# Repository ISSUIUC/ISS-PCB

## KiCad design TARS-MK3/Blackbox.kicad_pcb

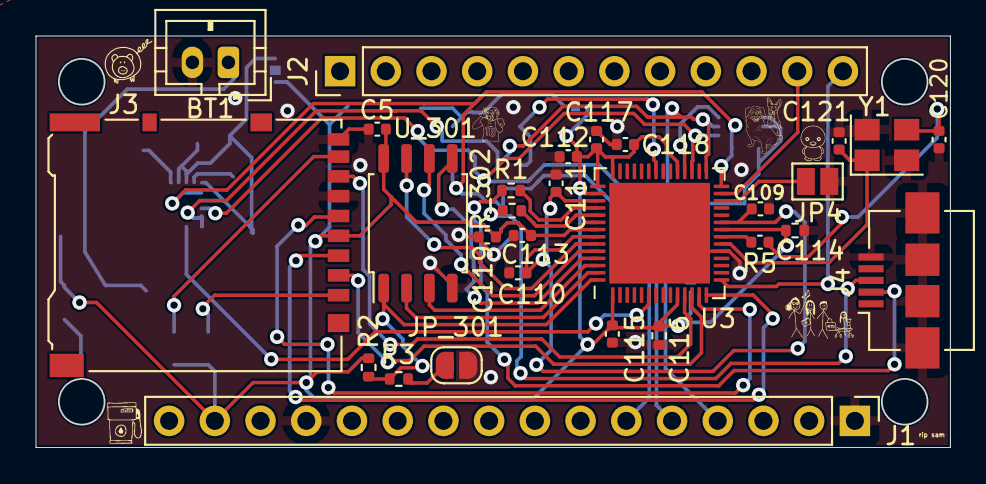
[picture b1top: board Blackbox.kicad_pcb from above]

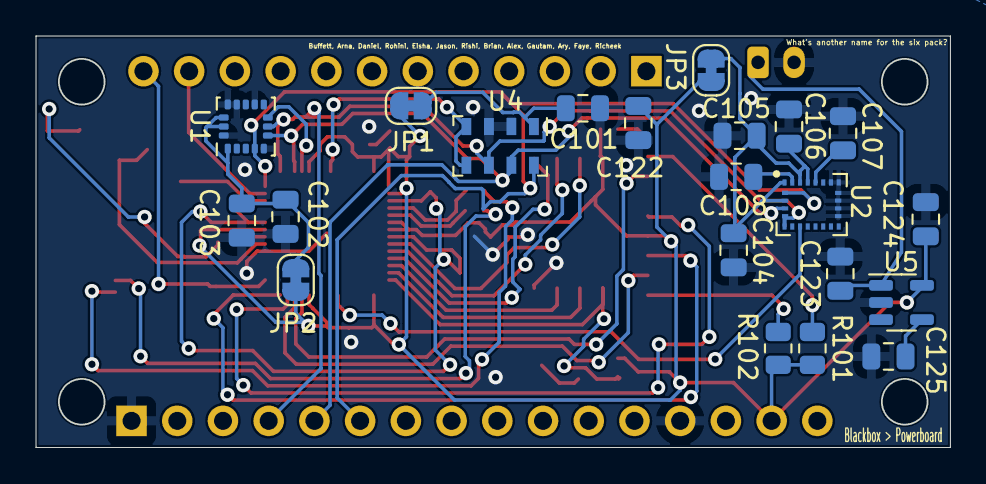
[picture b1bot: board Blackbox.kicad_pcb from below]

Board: 2 copper layers, 50.8 x 22.9 mm, 50 parts (21 on the bottom side), 39 nets.

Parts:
BT1: LiPo; JST_PH_B2B-PH-K_1x02_P2.00mm_Vertical
C5, C109, C110, C113, C115, C117, C118, C119: 100n; C_0402_1005Metric
C101: 100nF; C_0805_2012Metric
C102: 10uF; C_0805_2012Metric
C103: 0.1uF; C_0805_2012Metric
C104, C105, C108, C122: 100 nF; C_0805_2012Metric
C106: 10 uF; C_0805_2012Metric
C107: 10 nF; C_0805_2012Metric
C111, C112: 1u; C_0402_1005Metric
C114, C116: 100n; R_0402_1005Metric
C120, C121: LOAD_C; C_0402_1005Metric
C123, C124: 1uF; C_0805_2012Metric
C125: 10nF; C_0805_2012Metric
J1: RP Header 16 pin; PinHeader_1x16_P2.54mm_Vertical
J2: RP Header 12 pin; PinHeader_1x12_P2.54mm_Vertical
J3: Micro_SD_Card; microSD_HC_Hirose_DM3AT-SF-PEJM5
J4: USB_B_Micro; USB_Micro-B_Amphenol_10104110_Horizontal
JP1, JP2, JP3: Jumper_NC_Small; SolderJumper-2_P1.3mm_Bridged_RoundedPad1.0x1.5mm
JP4: Jumper; SolderJumper-2_P1.3mm_Open_Pad1.0x1.5mm
JP_301: Jumper; SolderJumper-2_P1.3mm_Open_RoundedPad1.0x1.5mm
R1: 27.4; R_0402_1005Metric
R2: DNF; R_0402_1005Metric
R3: R; R_0402_1005Metric
R5: 1k; C_0402_1005Metric
R101, R102: 10k; R_0805_2012Metric
R_302: 27.4; R_0402_1005Metric
U1: H3LIS331DL; LGA-16_3x3mm_P0.5mm_LayoutBorder3x5y
U2: LSM9DS1; LGA-24L_3x3.5mm_P0.43mm
U3: RP2040_chip; QFN-56-1EP_7x7mm_P0.4mm_EP5.6x5.6mm
U4: MS5611-01BA; LGA-8_3x5mm_P1.25mm
U5: LD3985M33R_SOT23; SOT-23-5
U_301: W25Q128JVS; SOIC-8_5.23x5.23mm_P1.27mm
Y1: Crystal_GND24; Crystal_SMD_3225-4Pin_3.2x2.5mm

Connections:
+1V1: C109.1, C110.1, C111.1, U3.23 (DVDD), U3.45 (VREG_VOUT), U3.50 (DVDD)
+3V3: C5.1, C112.1, C113.1, C114.1, C115.1, C116.1, C117.1, C118.1, C119.1, C122.2, C124.1, J1.15, J3.4 (VDD), JP1.1, JP2.1, JP3.1, R2.1, R101.1, R102.1, U3.1 (IOVDD), U3.10 (IOVDD), U3.22 (IOVDD), U3.33 (IOVDD), U3.42 (IOVDD), U3.43 (ADC_AVDD), U3.44 (VREG_VIN), U3.48 (USB_VDD), U3.49 (IOVDD), U5.5 (VOUT), U_301.8 (VCC)
/H3LIS331DL_CS: U1.8 (CS), U3.32 (GPIO21)
/I2C0_SCL: J2.11, U3.27 (GPIO16)
/I2C1_SDA: J2.12, U3.15 (GPIO12)
/LSM9_CS_M: U2.8 (CS_M), U3.6 (GPIO4)
/MS5611_CS: U3.36 (GPIO24), U4.4 (CSB), U4.5 (CSB)
/SNS_SPI_MISO: J1.4, U1.7 (SA0/SDO), U2.5 (SDO_A/G), U2.6 (SDO_M), U3.29 (GPIO18), U4.6 (SDO)
/SNS_SPI_MOSI: J1.5, U1.6 (SDA/SDI), U2.4 (SDA/SDI/SDO), U3.31 (GPIO20), U4.7 (SDI/SDA)
/SNS_SPI_SCK: J1.6, U1.4 (SCL/SCK), U2.2 (SCL/SPC), U3.28 (GPIO17), U4.8 (SCLK)
/SPI_SDCARD_CS: J3.2 (DAT3/CD), U3.12 (GPIO9)
/SPI_SDCARD_MISO: J3.7 (DAT0), U3.11 (GPIO8)
/SPI_SDCARD_MOSI: J3.3 (CMD), U3.14 (GPIO11)
/SPI_SDCARD_SCK: J3.5 (CLK), U3.13 (GPIO10)
/USB_D+: J4.3 (D+), R_302.1
/USB_D-: J4.2 (D-), R1.1
GND: BT1.2 (-), C5.2, C101.1, C102.2, C103.2, C104.2, C105.2, C106.2, C107.2, C108.2, C109.2, C110.2, C111.2, C112.2, C113.2, C114.2, C115.2, C116.2, C117.2, C118.2, C119.2, C120.2, C121.2, C122.1, C123.2, C124.2, C125.1, J1.1, J1.13, J3.6 (VSS), J3.9 (SHIELD), J4.5 (GND), J4.6 (Shield), JP4.1, JP_301.1, U1.5 (GND), U1.10 (GND), U1.12 (GND), U1.13 (GND), U1.16 (GND), U2.14 (RES), U2.15 (RES), U2.16 (RES), U2.17 (RES), U2.18 (RES), U2.19 (GND), U3.19 (TESTEN), U3.57 (GND), U4.2 (PS), U4.3 (GND), U5.2 (GND), U_301.4 (GND), Y1.2, Y1.4
unnamed: C101.2, JP1.2, U4.1 (VDD)
unnamed: C102.1, C103.1, JP2.2, U1.1 (VDDIO), U1.14 (VDD), U1.15 (VDD)
unnamed: C104.1, C105.1, C106.1, JP3.2, U2.1 (VDDIO), U2.3 (VDDIO), U2.22 (VDD), U2.23 (VDD)
unnamed: C107.1, U2.21 (CAP)
unnamed: C108.1, U2.24 (C1)
unnamed: C120.1, R5.2, Y1.3
unnamed: C121.1, U3.20 (XIN), Y1.1
unnamed: C125.2, U5.4 (BYP)
unnamed: J3.1 (DAT2), R102.2
unnamed: J3.8 (DAT1), R101.2
unnamed: JP4.2, U3.26 (RUN)
unnamed: JP_301.2, R3.1
unnamed: R1.2, U3.46 (USB_DM)
unnamed: R2.2, R3.2, U3.56 (QSPI_SS_N), U_301.1 (~CS)
unnamed: R5.1, U3.21 (XOUT)
unnamed: R_302.2, U3.47 (USB_DP)
unnamed: U3.51 (QSPI_SD3), U_301.7 (IO3)
unnamed: U3.52 (QSPI_SCLK), U_301.6 (CLK)
unnamed: U3.53 (QSPI_SD0), U_301.5 (DI(IO0))
unnamed: U3.54 (QSPI_SD2), U_301.3 (IO2)
unnamed: U3.55 (QSPI_SD1), U_301.2 (DO(IO1))
VBAT: BT1.1 (+), C123.1, U5.1 (VIN)

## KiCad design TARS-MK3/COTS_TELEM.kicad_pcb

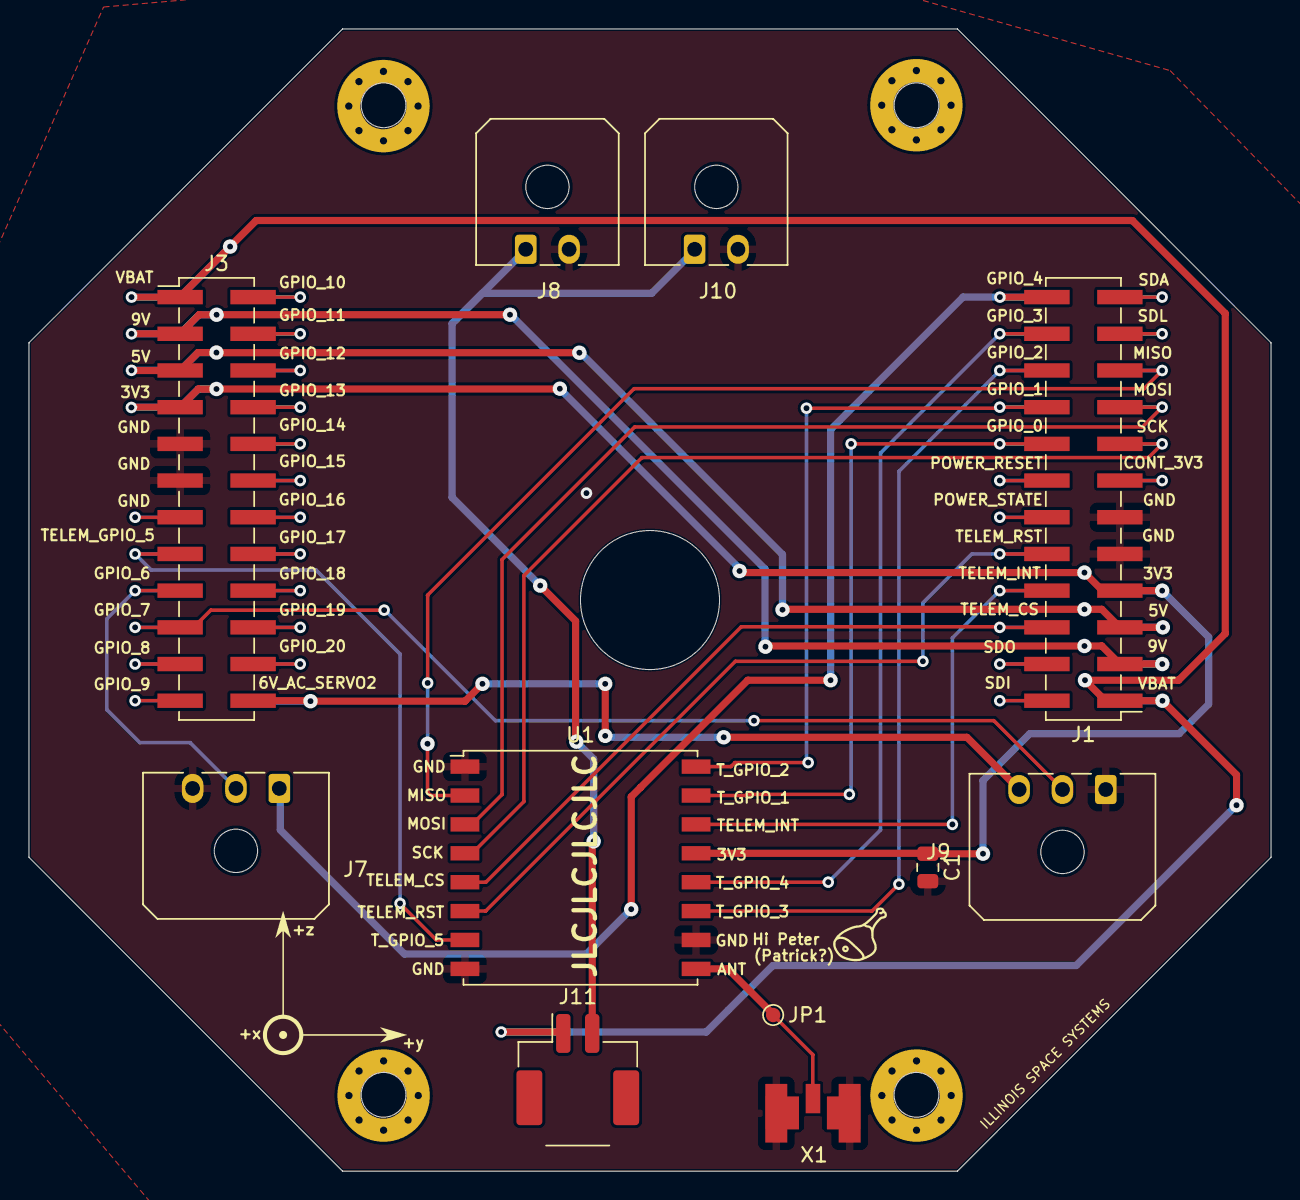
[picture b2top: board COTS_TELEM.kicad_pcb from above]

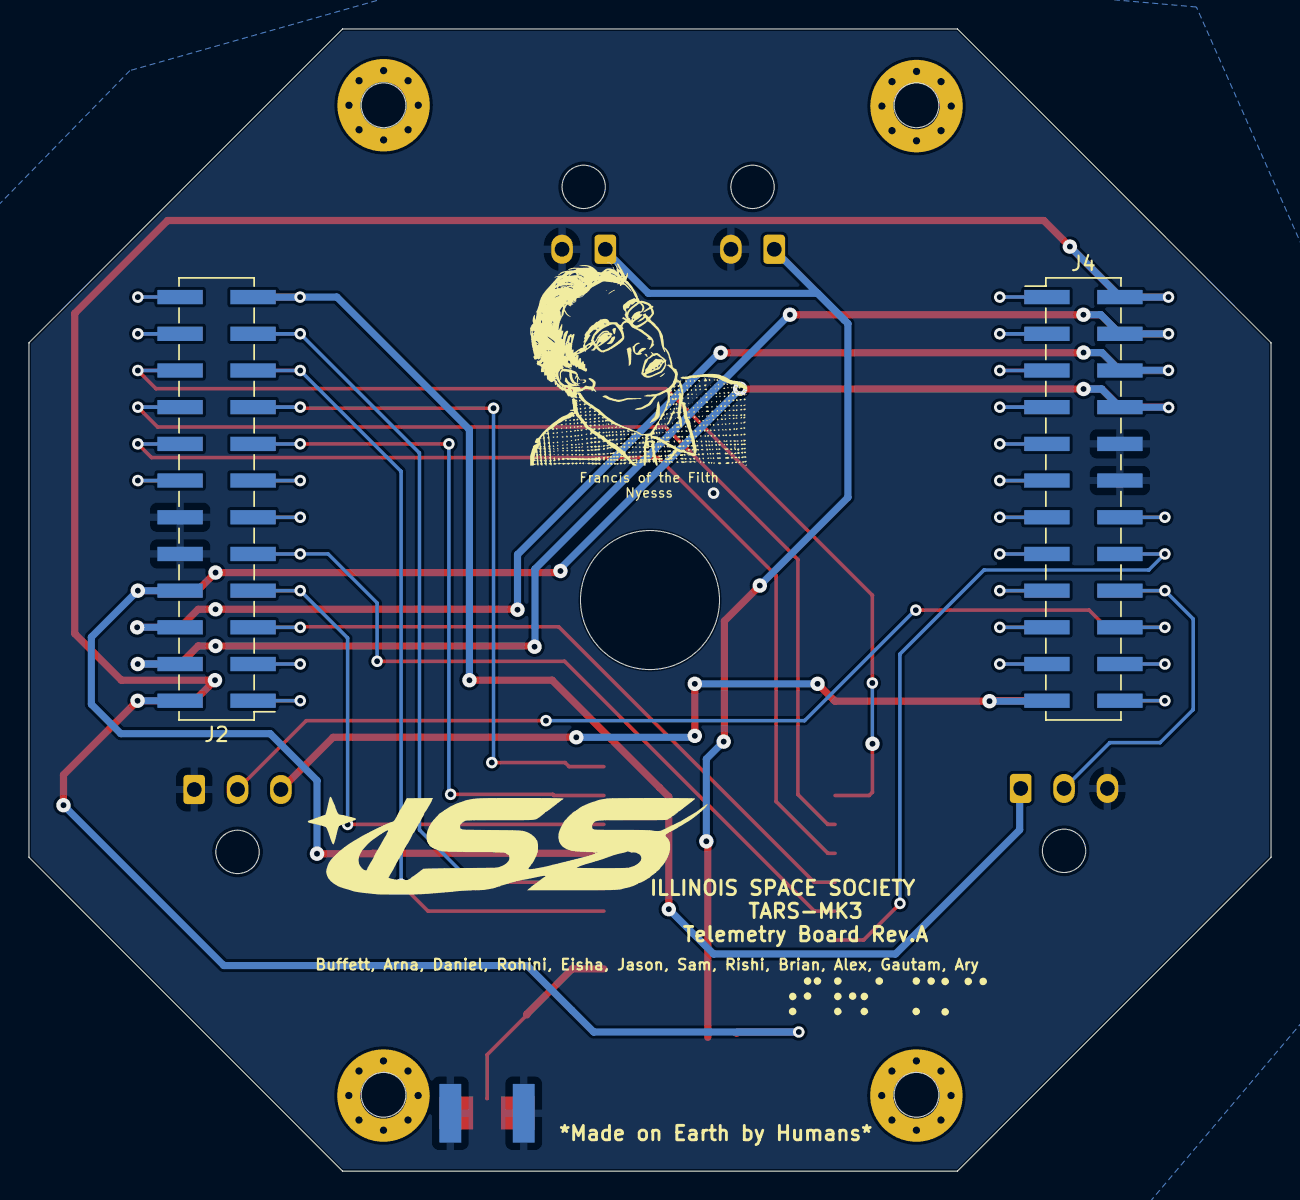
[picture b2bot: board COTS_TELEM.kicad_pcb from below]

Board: 2 copper layers, 86.0 x 79.1 mm, 13 parts (2 on the bottom side), 43 nets.

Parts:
C1: 10uF; C_0805_2012Metric
J1, J2, J3, J4: Conn_02x12_Odd_Even; PinHeader_2x12_P2.54mm_Vertical_SMD
J7, J9: Conn_01x03; Molex_Micro-Fit_3.0_43650-0300_1x03_P3.00mm_Horizontal
J8, J10: Conn_01x02; Molex_Micro-Fit_3.0_43650-0200_1x02_P3.00mm_Horizontal
J11: Conn_01x02; Molex_CLIK-Mate_502494-0270_1x02-1MP_P2.00mm_Horizontal
JP1: Conn_01x01_Female; TestPoint_Pad_D1.0mm
U1: RFM96W-433S2; HOPERF_RFM9XW_SMD
X1: uFL/SMA; uFL

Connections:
6V_AC_SERVO1: J1.24, J2.23, J7.1
6V_AC_SERVO2: J3.24, J4.23, J9.3
/3V3: C1.1, J1.7, J2.8, J3.7, J4.8, U1.13 (3.3V)
/5V: J1.5, J2.6, J3.5, J4.6
/9V: J1.3, J2.4, J3.3, J4.4
/B2B_GPIO_8: J3.21, J4.22
/B2B_GPIO_9: J3.23, J4.24
/B2B_GPIO_10: J3.2, J4.1
/B2B_GPIO_11: J3.4, J4.3
/B2B_GPIO_12: J3.6, J4.5
/B2B_GPIO_13: J3.8, J4.7
/B2B_GPIO_14: J3.10, J4.9
/B2B_GPIO_15: J3.12, J4.11
/B2B_GPIO_16: J3.14, J4.13
/B2B_GPIO_17: J3.16, J4.15
/B2B_GPIO_18: J3.18, J4.17
/B2B_GPIO_19: J3.20, J4.19
/B2B_GPIO_20: J3.22, J4.21
/B2B_I2C_SCL: J1.21, J2.22
/B2B_I2C_SDA: J1.23, J2.24
/B2B_SPI_MISO: J1.19, J2.20, U1.2 (MISO)
/B2B_SPI_MOSI: J1.17, J2.18, U1.3 (MOSI)
/B2B_SPI_SCK: J1.15, J2.16, U1.4 (SCK)
/B2B_UART_SDI: J1.2, J2.1
/B2B_UART_SDO: J1.4, J2.3
/CONT_3V3: J1.13, J2.14
/CONT_GND: J3.13, J4.14
/POWER_RESET: J1.14, J2.13
/POWER_STATE: J1.12, J2.11
/SERVO1: J3.17, J4.18, J7.2
/SERVO2: J3.19, J4.20, J9.2
/TELEM_CS: J1.6, J2.5, U1.5 (NSS)
/TELEM_GPIO_1: J1.16, J2.15, U1.15 (DIO1)
/TELEM_GPIO_2: J1.18, J2.17, U1.16 (DIO2)
/TELEM_GPIO_3: J1.20, J2.19, U1.11 (DIO3)
/TELEM_GPIO_4: J1.22, J2.21, U1.12 (DIO4)
/TELEM_GPIO_5: J3.15, J4.16, U1.7 (DIO5)
/TELEM_INT: J1.8, J2.7, U1.14 (DIO0)
/TELEM_RST: J1.10, J2.9, U1.6 (RESET)
/VBAT: J1.1, J2.2, J3.1, J4.2, J11.1
GND: C1.2, J1.9, J1.11, J2.10, J2.12, J3.9, J3.11, J4.10, J4.12, J7.3, J8.2, J9.1, J10.2, U1.1 (GND), U1.8 (GND), U1.10 (GND), X1.GND1, X1.GND2, X1.GND3, X1.GND4
unnamed: J8.1, J10.1, J11.2
unnamed: JP1.1, U1.9 (ANT), X1.ANTENNA (ANT)

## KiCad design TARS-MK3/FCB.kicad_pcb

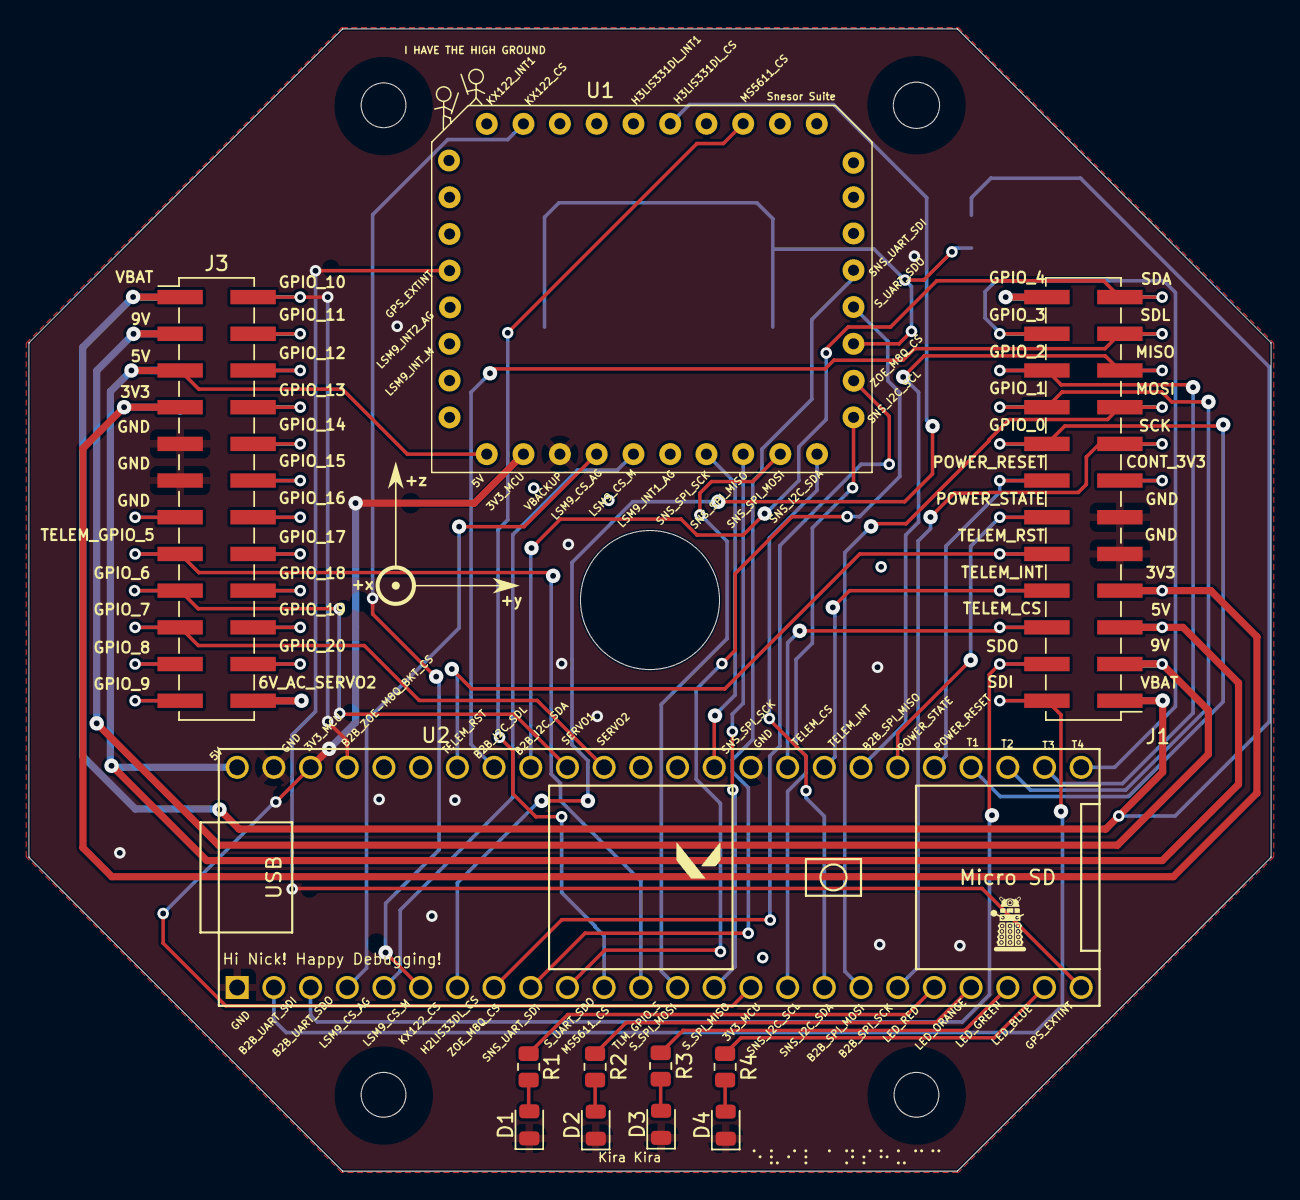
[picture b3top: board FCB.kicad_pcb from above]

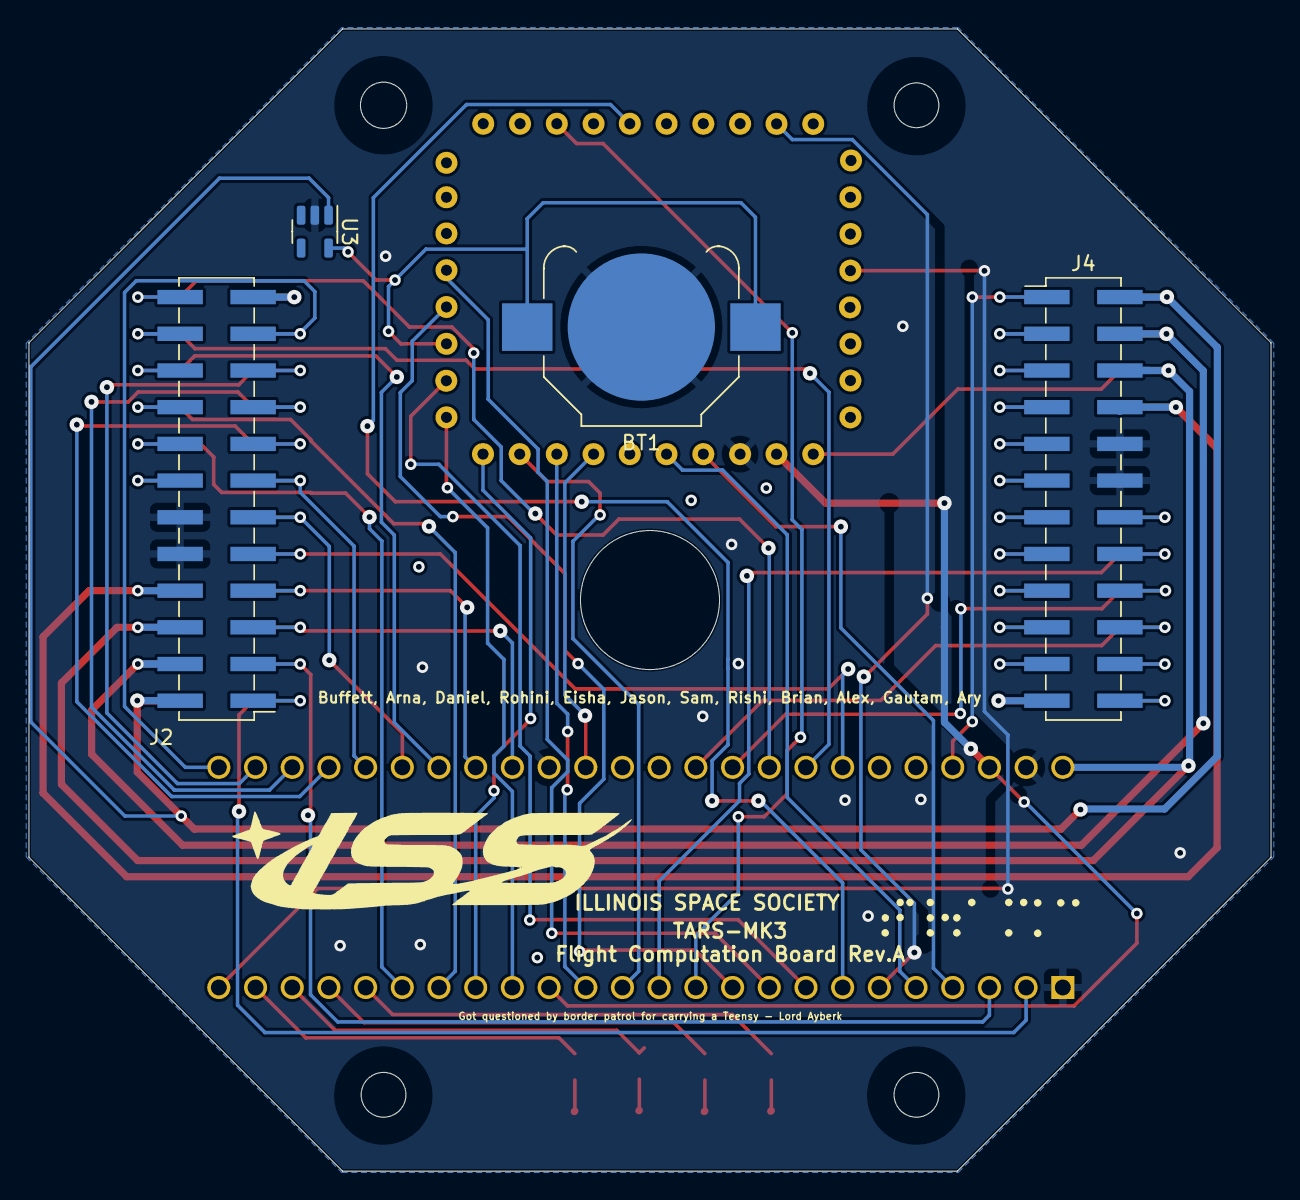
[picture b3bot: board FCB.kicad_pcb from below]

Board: 2 copper layers, 86.0 x 79.1 mm, 16 parts (4 on the bottom side), 65 nets.

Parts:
BT1: CR1225; BatteryHolder_Keystone_3000_1x12mm
D1, D2, D3, D4: LED; LED_0805_2012Metric
J1, J2, J3, J4: Conn_02x12_Odd_Even; PinHeader_2x12_P2.54mm_Vertical_SMD
R1, R2, R3, R4: 470; R_0805_2012Metric
U1: ISS_SENSOR_SUITE_V_1; General Sensor Module - 8x10 pin
U2: Teensy4.1_bare; Teensy41_bare
U3: LP2985-3.0; SOT-23-5

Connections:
6V_AC_SERVO1: J1.24, J2.23
6V_AC_SERVO2: J3.24, J4.23
/3V3: J1.7, J2.8, J3.7, J4.8
/3V3_MCU: U1.2 (3V3), U2.15 (3V3), U2.46 (3V3)
/5V: J1.5, J2.6, J3.5, J4.6, U1.1 (5V), U2.48 (VIN)
/9V: J1.3, J2.4, J3.3, J4.4
/B2B_GPIO_8: J3.21, J4.22
/B2B_GPIO_9: J3.23, J4.24
/B2B_GPIO_11: J3.4, J4.3
/B2B_GPIO_12: J3.6, J4.5
/B2B_GPIO_13: J3.8, J4.7
/B2B_GPIO_14: J3.10, J4.9
/B2B_GPIO_15: J3.12, J4.11
/B2B_GPIO_16: J3.14, J4.13
/B2B_GPIO_17: J3.16, J4.15
/B2B_GPIO_18: J3.18, J4.17
/B2B_GPIO_19: J3.20, J4.19
/B2B_GPIO_20: J3.22, J4.21
/B2B_I2C_SCL: J1.21, J2.22, U2.41 (19_A5_SCL)
/B2B_I2C_SDA: J1.23, J2.24, U2.40 (18_A4_SDA)
/B2B_SPI_MISO: J1.19, J2.20, U2.31 (39_MISO1_OUT1A)
/B2B_SPI_MOSI: J1.17, J2.18, U2.18 (26_A12_MOSI1)
/B2B_SPI_SCK: J1.15, J2.16, U2.19 (27_A13_SCK1)
/B2B_UART_SDI: J1.2, J2.1, U2.2 (0_RX1_CRX2_CS1)
/B2B_UART_SDO: J1.4, J2.3, U2.3 (1_TX1_CTX2_MISO1)
/B2B_ZOE_M8Q_BKT_CS: J3.2, J4.1, U2.45 (23_A9_CRX1_MCLK1)
/CONT_3V3: J1.13, J2.14
/CONT_GND: J3.13, J4.14
/GPS_EXTINT: U1.32 (ZOE_M8Q_INT), U2.24 (32_OUT1B)
/H3LIS331DL_CS: U1.23 (H3LIS331_CS), U2.7 (5_IN2)
/KX122_CS: U1.27 (KX134_CS), U2.6 (4_BCLK2)
/LED_BLUE: R4.1, U2.23 (31_CTX3)
/LED_GREEN: R3.1, U2.22 (30_CRX3)
/LED_ORANGE: R2.1, U2.21 (29_TX7)
/LED_RED: R1.1, U2.20 (28_RX7)
/LSM9_CS_AG: U1.4 (LSM9DS1_AG_CS), U2.4 (2_OUT2)
/LSM9_CS_M: U1.5 (LSM9DS1_M_CS), U2.5 (3_LRCLK2)
/MS5611_CS: U1.21 (MS5611_CS), U2.11 (9_OUT1C)
/POWER_RESET: J1.14, J2.13, U2.29 (37_CS)
/POWER_STATE: J1.12, J2.11, U2.30 (38_CS1_IN1)
/SERVO1: J3.17, J4.18, U2.39 (17_A3_TX4_SDA1)
/SERVO2: J3.19, J4.20, U2.38 (16_A2_RX4_SCL1)
/SNS_I2C_SCL: U1.11 (SCL0), U2.16 (24_A10_TX6_SCL2)
/SNS_I2C_SDA: U1.10 (SDA0), U2.17 (25_A11_RX6_SDA2)
/SNS_SPI_MISO: U1.8 (MISO0), U2.14 (12_MISO_MQSL)
/SNS_SPI_MOSI: U1.9 (MOSI0), U2.13 (11_MOSI_CTX1)
/SNS_SPI_SCK: U1.7 (SCK0), U2.35 (13_SCK_LED)
/SNS_UART_SDI: U1.15 (TX0), U2.9 (7_RX2_OUT1A)
/SNS_UART_SDO: U1.14 (RX0), U2.10 (8_TX2_IN1)
/TELEM_CS: J1.6, J2.5, U2.33 (41_A17)
/TELEM_GPIO_1: J1.16, J2.15, U2.28 (36_CS)
/TELEM_GPIO_2: J1.18, J2.17, U2.27 (35_TX8)
/TELEM_GPIO_3: J1.20, J2.19, U2.26 (34_RX8)
/TELEM_GPIO_4: J1.22, J2.21, U2.25 (33_MCLK2)
/TELEM_GPIO_5: J3.15, J4.16, U2.12 (10_CS_MQSR)
/TELEM_INT: J1.8, J2.7, U2.32 (40_A16)
/TELEM_RST: J1.10, J2.9, U2.42 (20_A6_TX5_LRCLK1)
/VBACKUP: BT1.1 (+), U1.13 (VBACKUP), U3.5 (VOUT)
/VBAT: J1.1, J2.2, J3.1, J4.2, U3.1 (VIN)
/ZOE-M8Q_CS: U1.12 (ZOE_M8Q_CS), U2.8 (6_OUT1D)
GND: BT1.2 (-), D1.1 (K), D2.1 (K), D3.1 (K), D4.1 (K), J1.9, J1.11, J2.10, J2.12, J3.9, J3.11, J4.10, J4.12, U1.3 (GND), U2.1 (GND), U2.34 (GND), U2.47 (GND), U3.2 (GND)
unnamed: D1.2 (A), R1.2
unnamed: D2.2 (A), R2.2
unnamed: D3.2 (A), R3.2
unnamed: D4.2 (A), R4.2

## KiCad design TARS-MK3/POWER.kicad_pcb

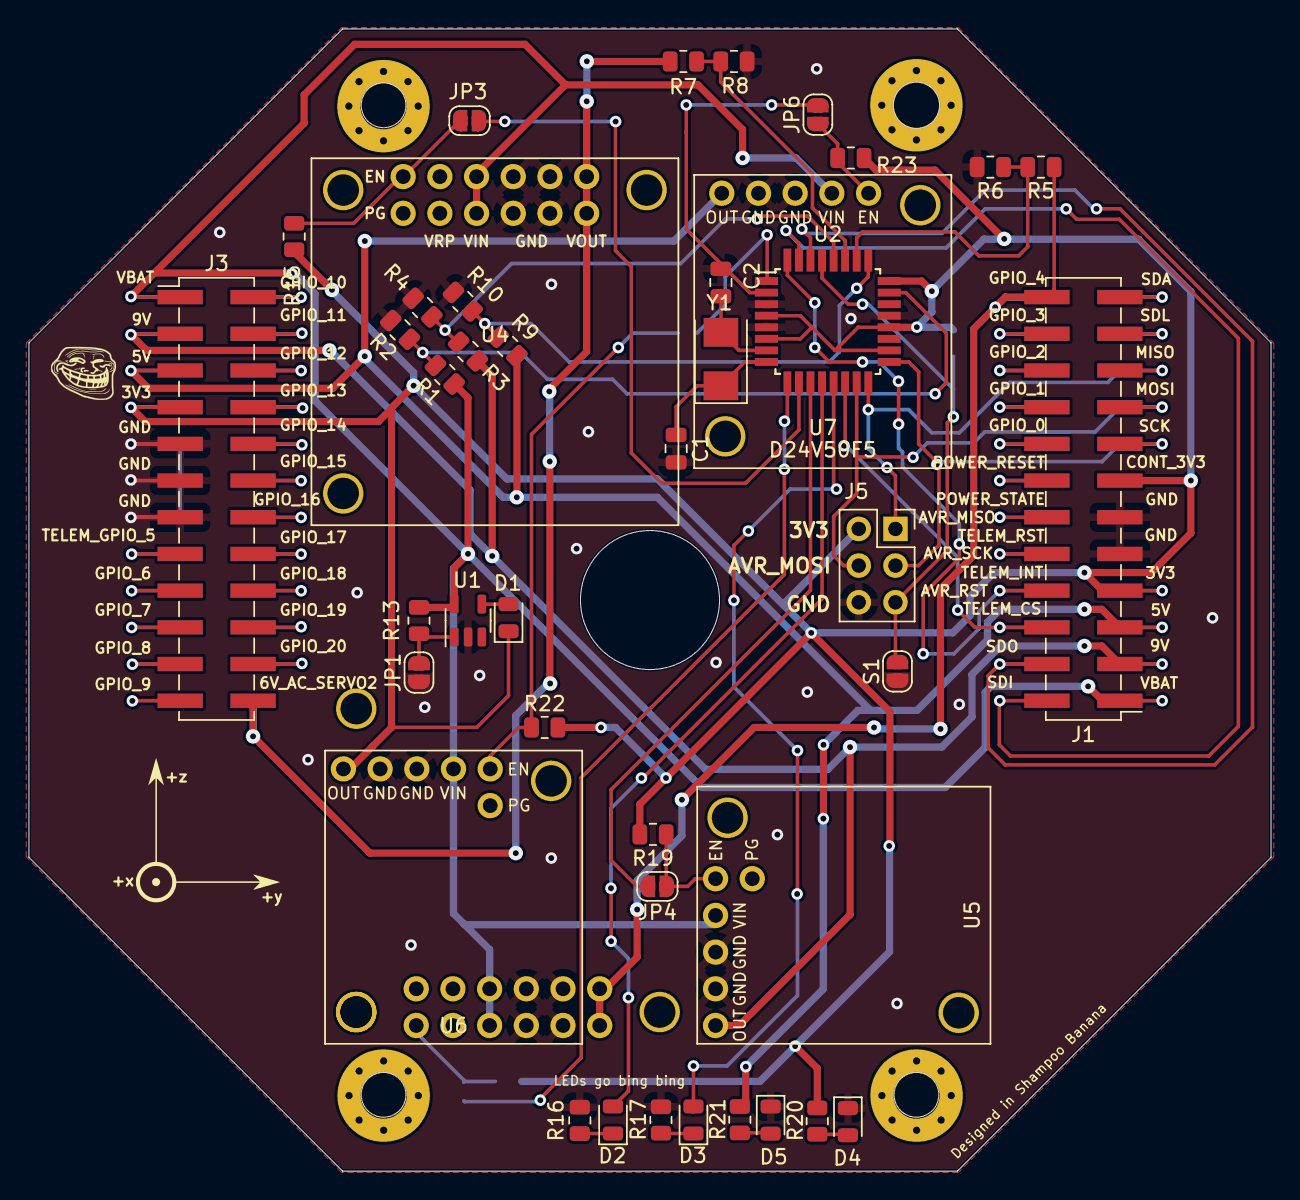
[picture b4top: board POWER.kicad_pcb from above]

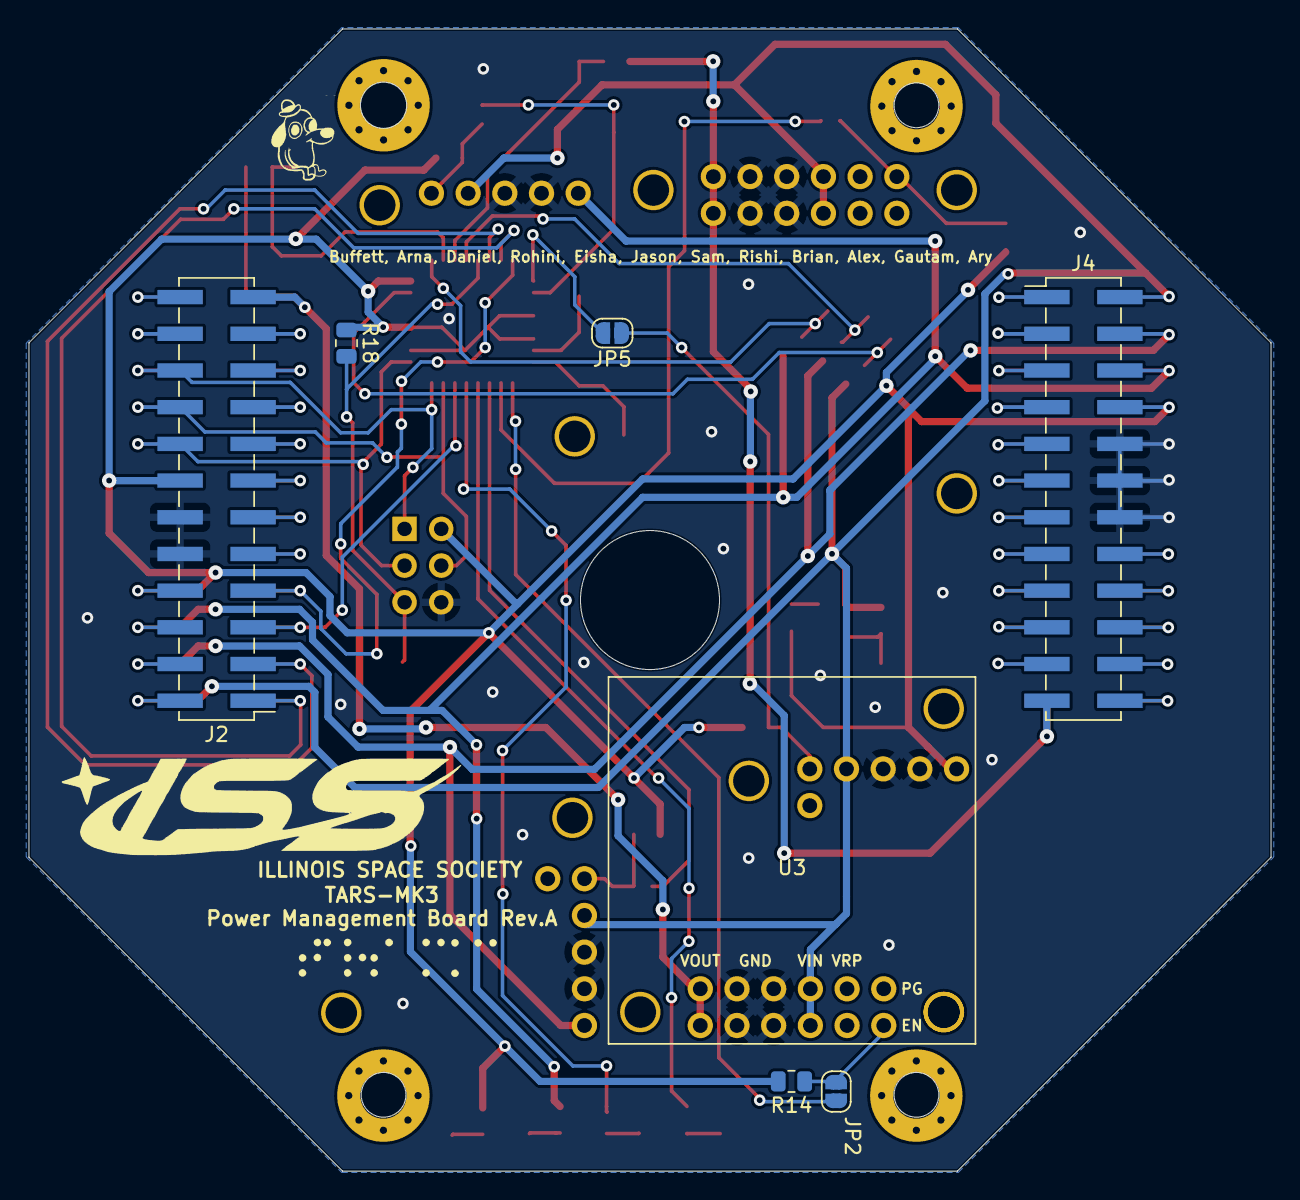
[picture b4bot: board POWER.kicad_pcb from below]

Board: 2 copper layers, 86.0 x 79.1 mm, 48 parts (7 on the bottom side), 65 nets.

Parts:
C1, C2: LOAD_C; C_0805_2012Metric
D1: D; D_0805_2012Metric
D2: GREEN; LED_0805_2012Metric
D3: ORANGE; LED_0805_2012Metric
D4: LED; LED_0805_2012Metric
D5: LED; D_0805_2012Metric
J1, J2, J3, J4: Conn_02x12_Odd_Even; PinHeader_2x12_P2.54mm_Vertical_SMD
J5: AVRISP; PinSocket_2x03_P2.54mm_Vertical
JP1, JP2, JP3, JP4, JP5, JP6: Jumper_2_Open; SolderJumper-2_P1.3mm_Open_RoundedPad1.0x1.5mm
R1, R3: 200kOhm; R_0805_2012Metric
R2, R4, R5, R6, R7, R8, R9, R10, R13, R14, R15, R19, R22, R23: 100kOhm; R_0805_2012Metric
R16, R17: 150Ω; R_0805_2012Metric
R18: 10k; R_0805_2012Metric
R20, R21: 1k; R_0805_2012Metric
S1: Reset; SolderJumper-2_P1.3mm_Open_RoundedPad1.0x1.5mm
U1: LK112M33TR; SOT-23-5
U2: ATmega328P-A; TQFP-32_7x7mm_P0.8mm
U3, U4: D36V50F6; D36V50F6-TARS
U5: D36V28F9; D36V28F3
U6: D36V28F3
U7: D24V50F5
Y1: 8Mhz; Crystal_SMD_5032-2Pin_5.0x3.2mm

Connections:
3V3: D1.1 (K), J1.7, J1.13, J2.8, J2.14, J3.7, J4.8, J5.2, R14.2, R15.2, R18.1, R19.2, R20.2, R22.2, R23.2, U2.4 (VCC), U2.6 (VCC), U2.18 (AVCC), U2.20 (AREF), U2.24 (PC1), U6.5 (OUT)
5V: J1.5, J2.6, J3.5, J4.6, R9.1, R21.1, U7.5 (OUT)
6V_AC_SERVO1: J1.24, J2.23, R5.1, U3.6 (VOUT), U3.12 (VOUT)
6V_AC_SERVO2: J3.24, J4.23, R7.1, U4.6 (VOUT), U4.12 (VOUT)
9V: J1.3, J2.4, J3.3, J4.4, R3.1, U5.5 (OUT)
/3V3_EN: JP5.2 (B), U2.1 (PD3)
/5V_EN: JP6.2 (B), U2.2 (PD4)
/5V_MONITOR: R9.2, R10.1, U2.25 (PC2)
/6V_AC_SERVO1_EN: JP2.2 (B), U2.9 (PD5)
/6V_AC_SERVO1_MONITOR: R5.2, R6.1, U2.26 (PC3)
/6V_AC_SERVO2_EN: JP3.2 (B), U2.10 (PD6)
/6V_AC_SERVO2_MONITOR: R7.2, R8.1, U2.27 (PC4)
/9V_EN: JP4.2 (B), U2.11 (PD7)
/9V_MONITOR: R3.2, R4.1, U2.28 (PC5)
/AVR_MISO: J1.19, J2.20, J5.1, U2.16 (PB4)
/AVR_MOSI: J1.17, J2.18, J5.4, U2.15 (PB3)
/AVR_RST: J5.5, R18.2, S1.2 (B), U2.29 (~RESET/PC6)
/AVR_SCK: J1.15, J2.16, J5.3, U2.17 (PB5)
/B2B_GPIO_6: J3.17, J4.18
/B2B_GPIO_7: J3.19, J4.20
/B2B_GPIO_8: J3.21, J4.22
/B2B_GPIO_9: J3.23, J4.24
/B2B_GPIO_10: J3.2, J4.1
/B2B_GPIO_11: J3.4, J4.3
/B2B_GPIO_12: J3.6, J4.5
/B2B_GPIO_13: J3.8, J4.7
/B2B_GPIO_14: J3.10, J4.9
/B2B_GPIO_15: J3.12, J4.11
/B2B_GPIO_16: J3.14, J4.13
/B2B_GPIO_17: J3.16, J4.15
/B2B_GPIO_18: J3.18, J4.17
/B2B_GPIO_19: J3.20, J4.19
/B2B_GPIO_20: J3.22, J4.21
/B2B_I2C_SCL: J1.21, J2.22
/B2B_I2C_SDA: J1.23, J2.24
/B2B_UART_SDI: J1.2, J2.1, U2.31 (PD1)
/B2B_UART_SDO: J1.4, J2.3, U2.30 (PD0)
/LED0: D2.2 (A), U2.12 (PB0)
/LED1: D3.2 (A), U2.13 (PB1)
/POWER_RESET: J1.14, J2.13
/POWER_STATE: J1.12, J2.11
/TELEM_CS: J1.6, J2.5, U2.14 (PB2)
/TELEM_GPIO_1: J1.16, J2.15
/TELEM_GPIO_2: J1.18, J2.17
/TELEM_GPIO_3: J1.20, J2.19
/TELEM_GPIO_4: J1.22, J2.21
/TELEM_GPIO_5: J3.15, J4.16
/TELEM_INT: J1.8, J2.7, U2.32 (PD2)
/TELEM_RST: J1.10, J2.9
/VBAT_MONITOR: R1.2, R2.1, U2.23 (PC0)
GND: C1.2, C2.2, D4.1 (K), D5.1 (K), J1.9, J1.11, J2.10, J2.12, J3.9, J3.11, J3.13, J4.10, J4.12, J4.14, J5.6, JP1.1 (A), R2.2, R4.2, R6.2, R8.2, R10.2, R16.2, R17.2, S1.1 (A), U1.2 (GND), U2.3 (GND), U2.5 (GND), U2.21 (GND), U3.4 (GND), U3.5 (GND), U3.10 (GND), U3.11 (GND), U4.4 (GND), U4.5 (GND), U4.10 (GND), U4.11 (GND), U5.3 (GND), U5.4 (GND), U6.3 (GND), U6.4 (GND), U7.3 (GND), U7.4 (GND)
unnamed: C1.1, U2.8 (XTAL2/PB7), Y1.1
unnamed: C2.1, U2.7 (XTAL1/PB6), Y1.2
unnamed: D1.2 (A), U1.4 (OUT)
unnamed: D2.1 (K), R16.1
unnamed: D3.1 (K), R17.1
unnamed: D4.2 (A), R20.1
unnamed: D5.2 (A), R21.2
unnamed: JP1.2 (B), R13.2, U1.1 (SHDN)
unnamed: JP2.1 (A), R14.1, U3.7 (EN)
unnamed: JP3.1 (A), R15.1, U4.7 (EN)
unnamed: JP4.1 (A), R19.1, U5.1 (EN)
unnamed: JP5.1 (A), R22.1, U6.1 (EN)
unnamed: JP6.1 (A), R23.1, U7.1 (EN)
VBAT: J1.1, J2.2, J3.1, J4.2, R1.1, R13.1, U1.5 (IN), U3.3 (VIN), U3.9 (VIN), U4.3 (VIN), U4.9 (VIN), U5.2 (VIN), U6.2 (VIN), U7.2 (VIN)

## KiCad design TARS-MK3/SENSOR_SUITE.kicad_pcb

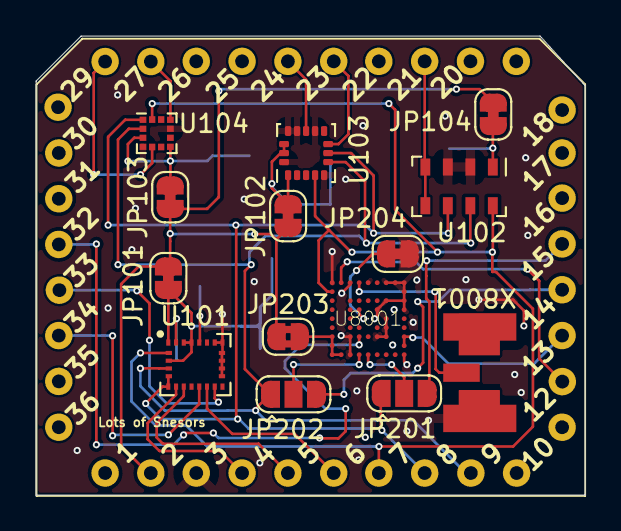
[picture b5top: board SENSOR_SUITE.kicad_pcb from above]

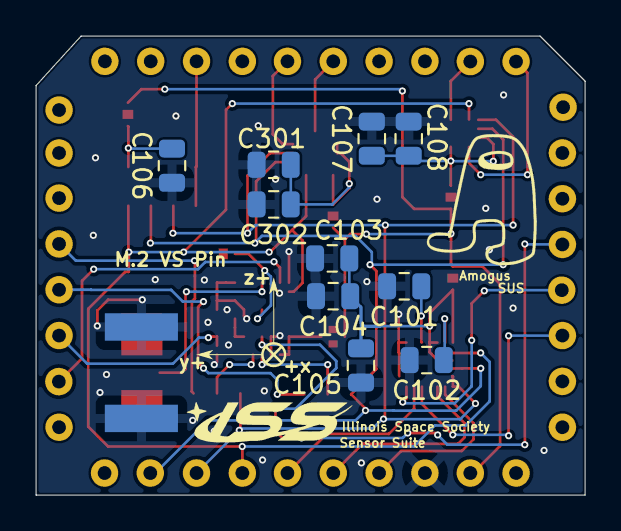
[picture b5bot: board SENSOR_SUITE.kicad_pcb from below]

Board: 2 copper layers, 30.5 x 25.5 mm, 25 parts (10 on the bottom side), 31 nets.

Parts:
C101: 10 nF; C_0805_2012Metric
C102, C103, C104: 100 nF; C_0805_2012Metric
C105: 10 uF; C_0805_2012Metric
C106, C107, C108: C_Small; C_0805_2012Metric
C301: 10uF; C_0805_2012Metric
C302: 0.1uF; C_0805_2012Metric
JP101, JP102, JP103, JP104, JP204: Jumper_NC_Small; SolderJumper-2_P1.3mm_Bridged_RoundedPad1.0x1.5mm
JP201, JP202: Jumper_3_Open; SolderJumper-3_P1.3mm_Open_RoundedPad1.0x1.5mm
JP203: Jumper_NC_Small; SolderJumper-2_P1.3mm_Bridged2Bar_RoundedPad1.0x1.5mm
U1: ISS_SENSOR_SUITE_V_1; General Sensor Module - 8x10 pin
U101: LSM9DS1; LGA-24L_3x3.5mm_P0.43mm
U102: MS5611-01BA; LGA-8_3x5mm_P1.25mm
U103: H3LIS331DL; LGA-16_3x3mm_P0.5mm_LayoutBorder3x5y
U104: KX122-1042; LGA-12_2x2mm_P0.5mm
U8001: ZOE-M8Q
X8001: SMACONNECTOR; uFL

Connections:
3V3: JP101.1, JP102.1, JP103.1, JP104.1, JP203.1, U1.2 (3V3)
/H3LIS331DL_CS: U1.23 (H3LIS331_CS), U103.8 (CS)
/H3LIS331DL_INT1: U1.24 (H3LIS331_INT1), U103.11 (INT1)
/KX122_CS: U1.27 (KX134_CS), U104.10 (~CS)
/KX122_INT1: U1.28 (KX134_INT1), U104.5 (INT1)
/LSM9_CS_AG: U1.4 (LSM9DS1_AG_CS), U101.7 (CS_A/G)
/LSM9_CS_M: U1.5 (LSM9DS1_M_CS), U101.8 (CS_M)
/LSM9_INT1_AG: U1.6 (LSM9DS1_AG_INT1), U101.11 (INT1_A/G)
/LSM9_INT2_AG: U1.33 (LSM9DS1_AG_INT2), U101.12 (INT2_A/G)
/LSM9_INT_M: U1.34 (LSM9DS1_M_INT), U101.10 (INT_M)
/MS5611_CS: U1.21 (MS5611_CS), U102.4 (CSB), U102.5 (CSB)
GND: C101.2, C102.2, C103.2, C104.2, C105.2, C106.1, C107.2, C108.2, C301.2, C302.2, JP204.1, U1.3 (GND), U101.14 (RES), U101.15 (RES), U101.16 (RES), U101.17 (RES), U101.18 (RES), U101.19 (GND), U102.2 (PS), U102.3 (GND), U103.5 (GND), U103.10 (GND), U103.12 (GND), U103.13 (GND), U103.16 (GND), U104.4 (TRIG), U104.9 (GND), U8001.P$A1 (A1_GND), U8001.P$A3 (A3_GND), U8001.P$A5 (A5_GND), U8001.P$A7 (A7_GND), U8001.P$A8 (A8_GND), U8001.P$A9 (A9_GND), U8001.P$B9 (B9_GND), U8001.P$C7 (C7_GND), U8001.P$C9 (C9_GND), U8001.P$D6 (D6_GND), U8001.P$D9 (D9_GND), U8001.P$E7 (E7_GND), U8001.P$F7 (F7_GND), U8001.P$G3 (G3_GND), U8001.P$G6 (G6_GND), U8001.P$G7 (G7_GND), U8001.P$J3 (J3_GND), U8001.P$J9 (J9_GND), X8001.GND1, X8001.GND2, X8001.GND3, X8001.GND4
GPS_EXTINT: U1.32 (ZOE_M8Q_INT), U8001.P$G4 (G4_PIO13/EXTINT)
unnamed: C101.1, U101.21 (CAP)
unnamed: C102.1, U101.24 (C1)
unnamed: C103.1, C104.1, C105.1, JP101.2, U101.1 (VDDIO), U101.3 (VDDIO), U101.22 (VDD), U101.23 (VDD)
unnamed: C106.2, JP104.2, U102.1 (VDD)
unnamed: C107.1, C108.1, JP103.2, U104.3 (IO_VDD), U104.7 (VDD)
unnamed: C301.1, C302.1, JP102.2, U103.1 (VDDIO), U103.14 (VDD), U103.15 (VDD)
unnamed: JP201.2 (C), U8001.P$J5 (J5_TXD/SPI_MISO)
unnamed: JP202.2 (C), U8001.P$J4 (J4_RXD/SPI_MOSI)
unnamed: JP203.2, U8001.P$G1 (G1_VCC), U8001.P$H1 (H1_VCC), U8001.P$J1 (J1_VCC), U8001.P$J2 (J2_VCC)
unnamed: JP204.2, U8001.P$D4 (D4_D_SEL)
unnamed: U8001.P$A4 (A4_RF_IN), X8001.ANTENNA (ANT)
SNS_SPI_MISO: JP201.1 (A), U1.8 (MISO0), U101.5 (SDO_A/G), U101.6 (SDO_M), U102.6 (SDO), U103.7 (SA0/SDO), U104.1 (SDO/ADDR)
SNS_SPI_MOSI: JP202.1 (A), U1.9 (MOSI0), U101.4 (SDA/SDI/SDO), U102.7 (SDI/SDA), U103.6 (SDA/SDI), U104.2 (SDI/SDA)
SNS_SPI_SCK: U1.7 (SCK0), U101.2 (SCL/SPC), U102.8 (SCLK), U103.4 (SCL/SCK), U104.12 (SCLK/SCL), U8001.P$B1 (B1_SCL/SPI_CLK)
SNS_UART_SDI: JP201.3 (B), U1.15 (TX0)
SNS_UART_SDO: JP202.3 (B), U1.14 (RX0)
VBAT0: U1.13 (VBACKUP), U8001.P$G9 (G9_RESERVED), U8001.P$H9 (H9_V_BCKP)
ZOE_M8Q_CS: U1.12 (ZOE_M8Q_CS), U8001.P$A2 (A2_SDA/SPI_CS_N)
